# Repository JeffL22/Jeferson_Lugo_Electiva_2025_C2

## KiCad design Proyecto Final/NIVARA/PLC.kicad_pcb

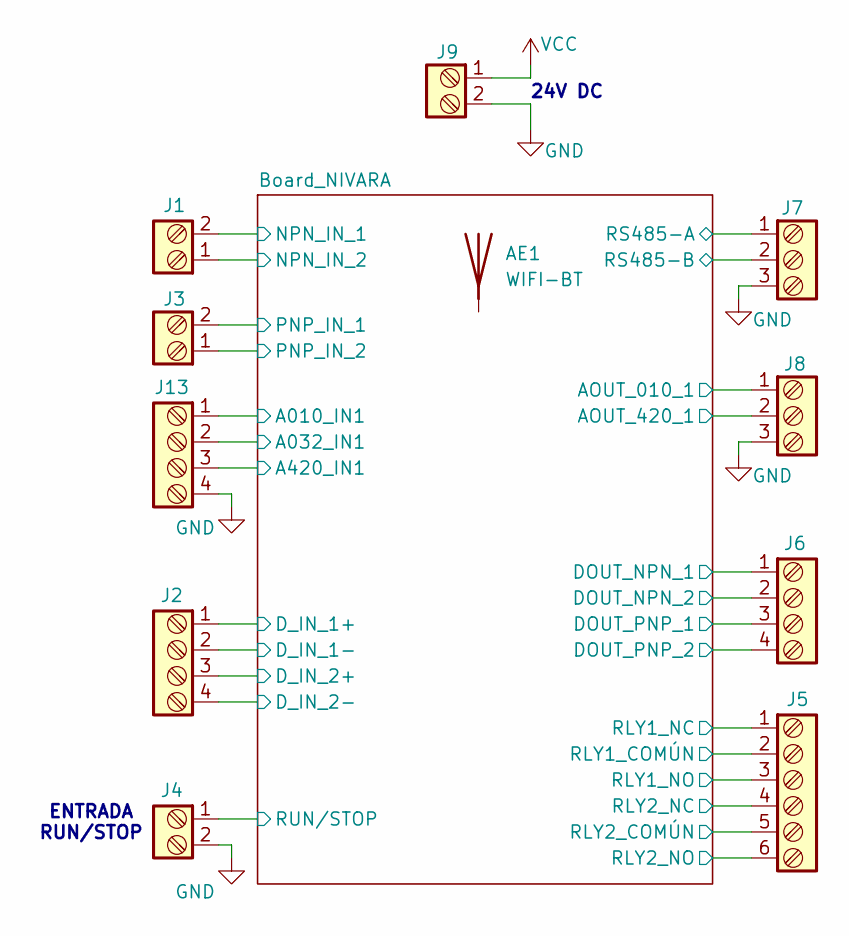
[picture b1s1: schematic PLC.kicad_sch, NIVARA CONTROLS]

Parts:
AE1: WIFI-BT
J1, J3, J4, J9: Screw_Terminal_2_P5.00mm; TerminalBlock_Phoenix_PT-1,5-2-5.0-H_1x02_P5.00mm_Horizontal
J2, J6, J13: Screw_Terminal_4_P5.00mm; TerminalBlock_Phoenix_PT-1,5-4-5.0-H_1x04_P5.00mm_Horizontal
J5: Screw_Terminal_6_P5.00mm; TerminalBlock_Phoenix_PT-1,5-6-5.0-H_1x06_P5.00mm_Horizontal
J7, J8: Screw_Terminal_3_P5.00mm; TerminalBlock_Phoenix_PT-1,5-3-5.0-H_1x03_P5.00mm_Horizontal

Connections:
/Board_NIVARA/A010_IN1: J13.1; also elsewhere on the board
/Board_NIVARA/A032_IN1: J13.2; also elsewhere on the board
/Board_NIVARA/A420_IN1: J13.3; also elsewhere on the board
/Board_NIVARA/AOUT_010_1: J8.1; also elsewhere on the board
/Board_NIVARA/AOUT_420_1: J8.2; also elsewhere on the board
/Board_NIVARA/DOUT_NPN_1: J6.1; also elsewhere on the board
/Board_NIVARA/DOUT_NPN_2: J6.2; also elsewhere on the board
/Board_NIVARA/DOUT_PNP_1: J6.3; also elsewhere on the board
/Board_NIVARA/DOUT_PNP_2: J6.4; also elsewhere on the board
/Board_NIVARA/D_IN_1+: J2.1; also elsewhere on the board
/Board_NIVARA/D_IN_2+: J2.3; also elsewhere on the board
/Board_NIVARA/NPN_IN_1: J1.2; also elsewhere on the board
/Board_NIVARA/NPN_IN_2: J1.1; also elsewhere on the board
/Board_NIVARA/PNP_IN_1: J3.2; also elsewhere on the board
/Board_NIVARA/PNP_IN_2: J3.1; also elsewhere on the board
/Board_NIVARA/RLY1_COMÚN: J5.2; also elsewhere on the board
/Board_NIVARA/RLY1_NC: J5.1; also elsewhere on the board
/Board_NIVARA/RLY1_NO: J5.3; also elsewhere on the board
/Board_NIVARA/RLY2_COMÚN: J5.5; also elsewhere on the board
/Board_NIVARA/RLY2_NC: J5.4; also elsewhere on the board
/Board_NIVARA/RLY2_NO: J5.6; also elsewhere on the board
/Board_NIVARA/RS485-A: J7.1; also elsewhere on the board
/Board_NIVARA/RS485-B: J7.2; also elsewhere on the board
/Board_NIVARA/RUN/STOP: J4.1
GND: J2.2, J2.4, J4.2, J7.3, J8.3, J9.2, J13.4; also elsewhere on the board
VCC: J9.1; also elsewhere on the board

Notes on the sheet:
24V DC
ENTRADA RUN/STOP

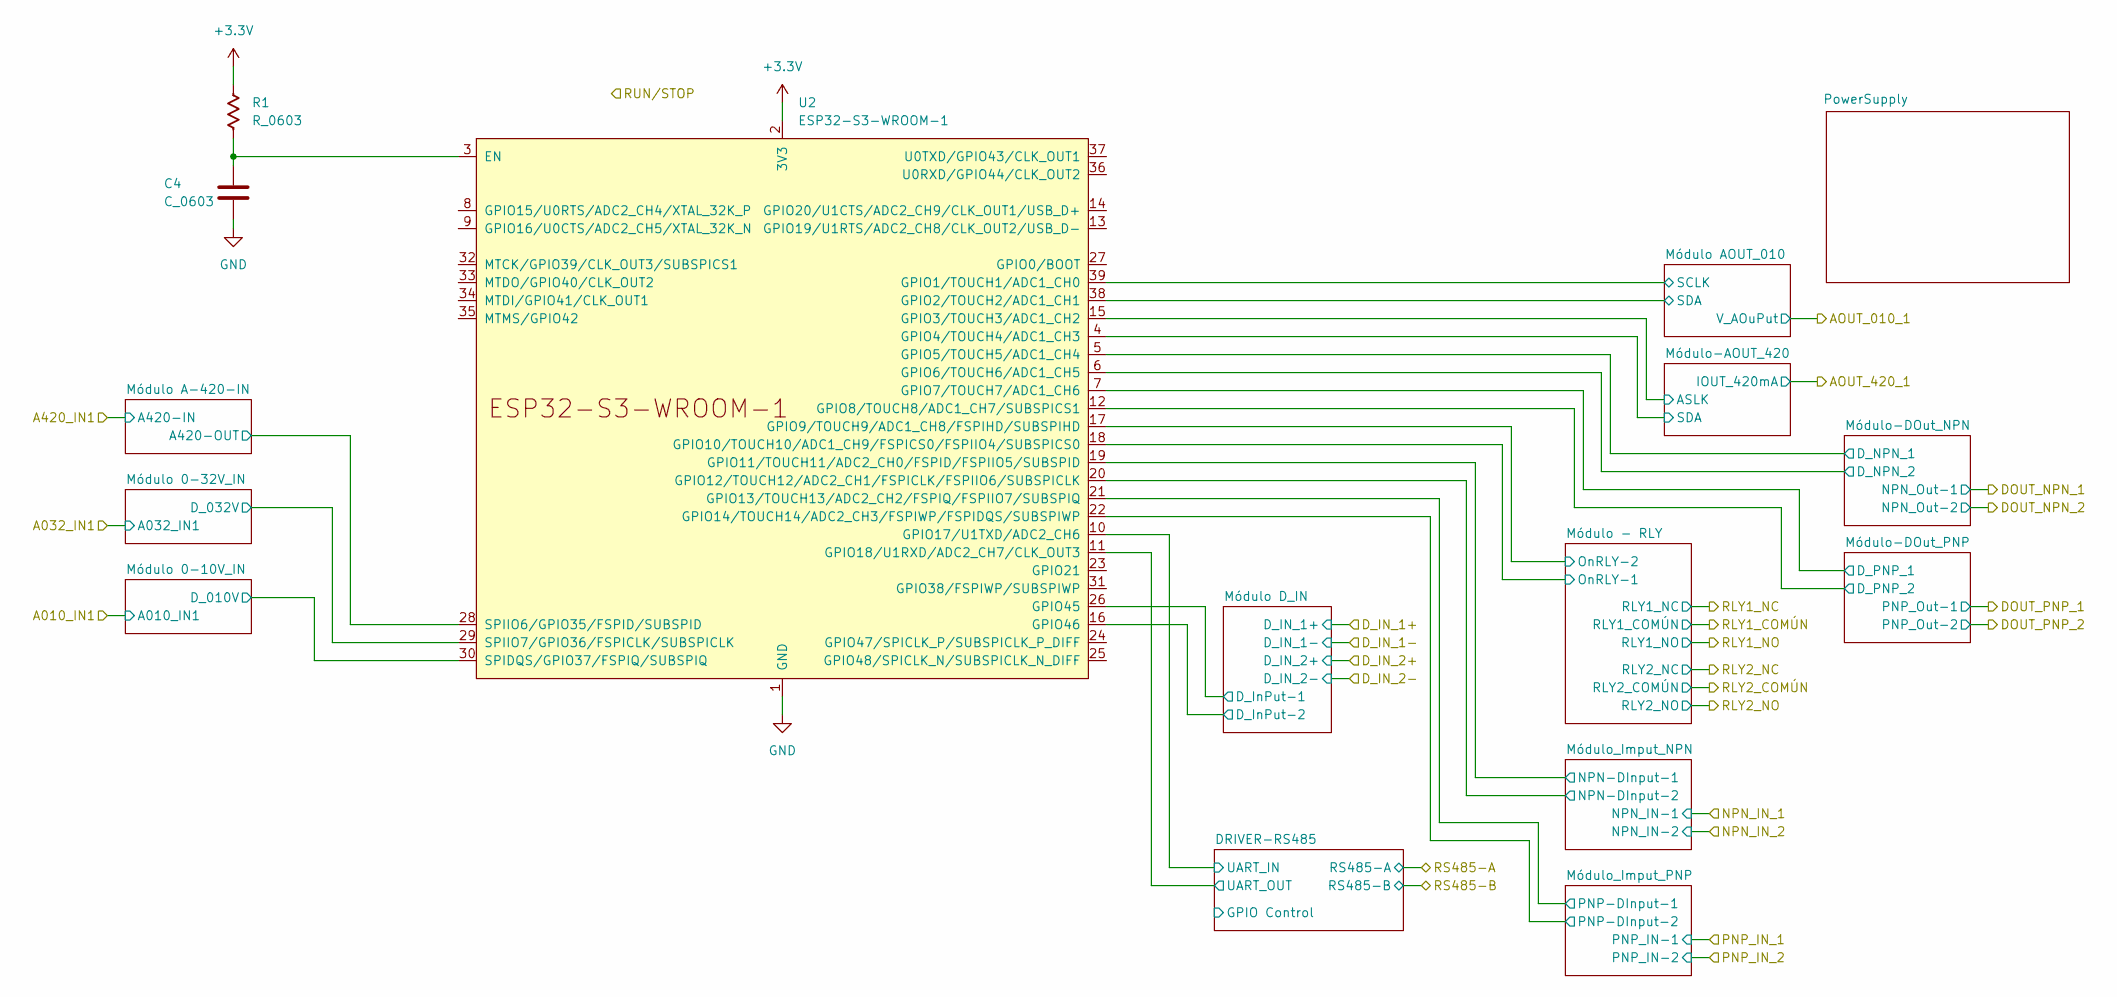
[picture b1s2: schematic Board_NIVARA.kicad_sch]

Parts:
C4: C_0603; C_0603_1608Metric
R1: R_0603; R_0603_1608Metric
U2: ESP32-S3-WROOM-1

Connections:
+3.3V: R1.1, U2.2 (3V3); also elsewhere on the board
/Board_NIVARA/A420_IN1: U2.28 (SPIIO6/GPIO35/FSPID/SUBSPID); also elsewhere on the board
/Board_NIVARA/DRIVER-RS485/UART_IN: U2.10 (GPIO17/U1TXD/ADC2_CH6); also elsewhere on the board
/Board_NIVARA/DRIVER-RS485/UART_OUT: U2.11 (GPIO18/U1RXD/ADC2_CH7/CLK_OUT3); also elsewhere on the board
/Board_NIVARA/Módulo 0-10V_IN/D_010V: U2.30 (SPIDQS/GPIO37/FSPIQ/SUBSPIQ); also elsewhere on the board
/Board_NIVARA/Módulo 0-32V_IN/D_032V: U2.29 (SPIIO7/GPIO36/FSPICLK/SUBSPICLK); also elsewhere on the board
/Board_NIVARA/Módulo - RLY/OnRLY-1: U2.18 (GPIO10/TOUCH10/ADC1_CH9/FSPICS0/FSPIIO4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); also elsewhere on the board
/Board_NIVARA/Módulo - RLY/OnRLY-2: U2.17 (GPIO9/TOUCH9/ADC1_CH8/FSPIHD/SUBSPIHD); also elsewhere on the board
/Board_NIVARA/Módulo AOUT_010/SCLK: U2.39 (GPIO1/TOUCH1/ADC1_CH0); also elsewhere on the board
/Board_NIVARA/Módulo AOUT_010/SDA: U2.38 (GPIO2/TOUCH2/ADC1_CH1); also elsewhere on the board
/Board_NIVARA/Módulo D_IN/D_InPut-1: U2.26 (GPIO45); also elsewhere on the board
/Board_NIVARA/Módulo D_IN/D_InPut-2: U2.16 (GPIO46); also elsewhere on the board
/Board_NIVARA/Módulo-AOUT_420/ASLK: U2.15 (GPIO3/TOUCH3/ADC1_CH2); also elsewhere on the board
/Board_NIVARA/Módulo-AOUT_420/SDA: U2.4 (GPIO4/TOUCH4/ADC1_CH3); also elsewhere on the board
/Board_NIVARA/Módulo-DOut_NPN/D_NPN_1: U2.5 (GPIO5/TOUCH5/ADC1_CH4); also elsewhere on the board
/Board_NIVARA/Módulo-DOut_NPN/D_NPN_2: U2.6 (GPIO6/TOUCH6/ADC1_CH5); also elsewhere on the board
/Board_NIVARA/Módulo-DOut_PNP/D_PNP_1: U2.7 (GPIO7/TOUCH7/ADC1_CH6); also elsewhere on the board
/Board_NIVARA/Módulo-DOut_PNP/D_PNP_2: U2.12 (GPIO8/TOUCH8/ADC1_CH7/SUBSPICS1); also elsewhere on the board
/Board_NIVARA/Módulo_Imput_NPN/NPN-DInput-1: U2.19 (GPIO11/TOUCH11/ADC2_CH0/FSPID/FSPIIO5/S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); also elsewhere on the board
/Board_NIVARA/Módulo_Imput_NPN/NPN-DInput-2: U2.20 (GPIO12/TOUCH12/ADC2_CH1/FSPICLK/FSPIIO6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); also elsewhere on the board
/Board_NIVARA/Módulo_Imput_PNP/PNP-DInput-1: U2.21 (GPIO13/TOUCH13/ADC2_CH2/FSPIQ/FSPIIO7/S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); also elsewhere on the board
/Board_NIVARA/Módulo_Imput_PNP/PNP-DInput-2: U2.22 (GPIO14/TOUCH14/ADC2_CH3/FSPIWP/FSPIDQS/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); also elsewhere on the board
GND: C4.2, U2.1 (GND), U2.40 (GND), U2.41 (GND); also elsewhere on the board
unnamed: C4.1, R1.2, U2.3 (EN)

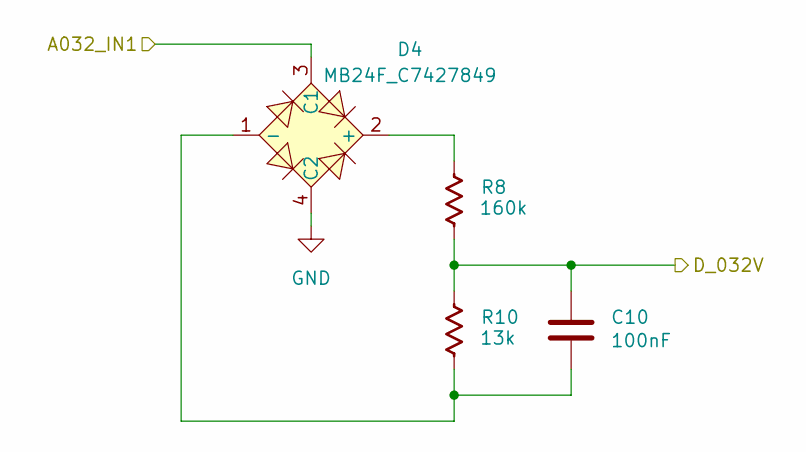
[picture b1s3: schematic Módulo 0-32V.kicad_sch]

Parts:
C10: C_0805; C_0805_2012Metric
D4: MB24F_C7427849; MB24F-SMD_L4.7-W3.8-P2.50-LS6.8-BL; LCSC Part C7427849
R8, R10: R_0603; R_0603_1608Metric

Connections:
/Board_NIVARA/A032_IN1: D4.3 (C1); also elsewhere on the board
/Board_NIVARA/Módulo 0-32V_IN/D_032V: C10.1, R8.2, R10.1; also elsewhere on the board
GND: D4.4 (C2); also elsewhere on the board
unnamed: D4.2 (+), R8.1
unnamed: C10.2, D4.1 (-), R10.2

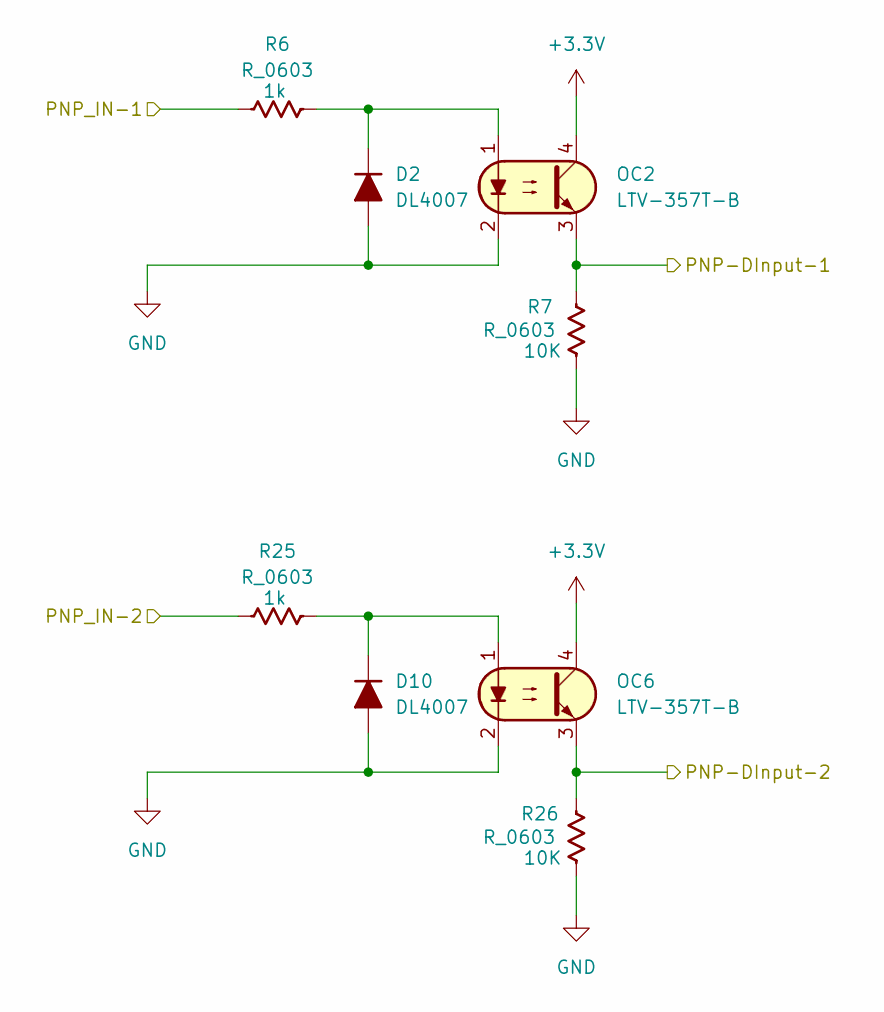
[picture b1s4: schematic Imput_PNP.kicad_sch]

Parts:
D2, D10: DL4007; D_0805_2012Metric_Pad1.15x1.40mm_HandSolder
OC2, OC6: LTV-357T-B; SO-4_4.4x3.9mm_P2.54mm
R6, R7, R25, R26: R_0603; R_0603_1608Metric

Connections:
+3.3V: OC2.4, OC6.4; also elsewhere on the board
/Board_NIVARA/Módulo_Imput_PNP/PNP-DInput-1: OC2.3, R7.2; also elsewhere on the board
/Board_NIVARA/Módulo_Imput_PNP/PNP-DInput-2: OC6.3, R26.2; also elsewhere on the board
/Board_NIVARA/PNP_IN_1: R6.1; also elsewhere on the board
/Board_NIVARA/PNP_IN_2: R25.1; also elsewhere on the board
GND: D2.2 (A), D10.2 (A), OC2.2, OC6.2, R7.1, R26.1; also elsewhere on the board
unnamed: D2.1 (K), OC2.1, R6.2
unnamed: D10.1 (K), OC6.1, R25.2

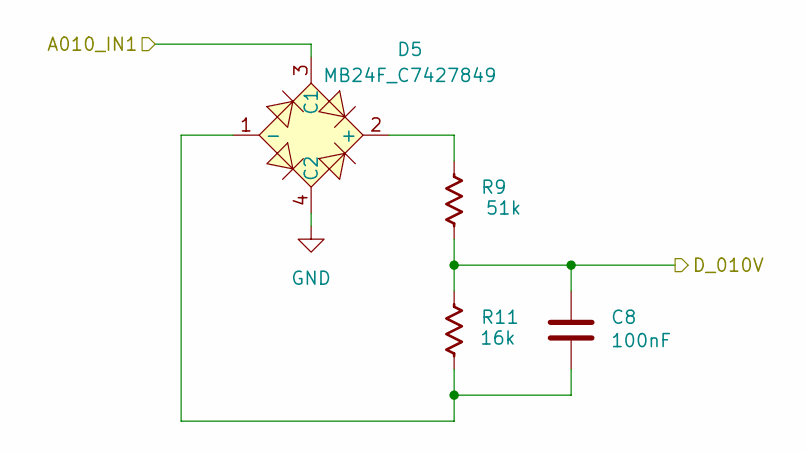
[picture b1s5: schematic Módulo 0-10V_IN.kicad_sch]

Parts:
C8: C_0805; C_0805_2012Metric
D5: MB24F_C7427849; MB24F-SMD_L4.7-W3.8-P2.50-LS6.8-BL; LCSC Part C7427849
R9, R11: R_0603; R_0603_1608Metric

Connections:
/Board_NIVARA/A010_IN1: D5.3 (C1); also elsewhere on the board
/Board_NIVARA/Módulo 0-10V_IN/D_010V: C8.1, R9.2, R11.1; also elsewhere on the board
GND: D5.4 (C2); also elsewhere on the board
unnamed: D5.2 (+), R9.1
unnamed: C8.2, D5.1 (-), R11.2

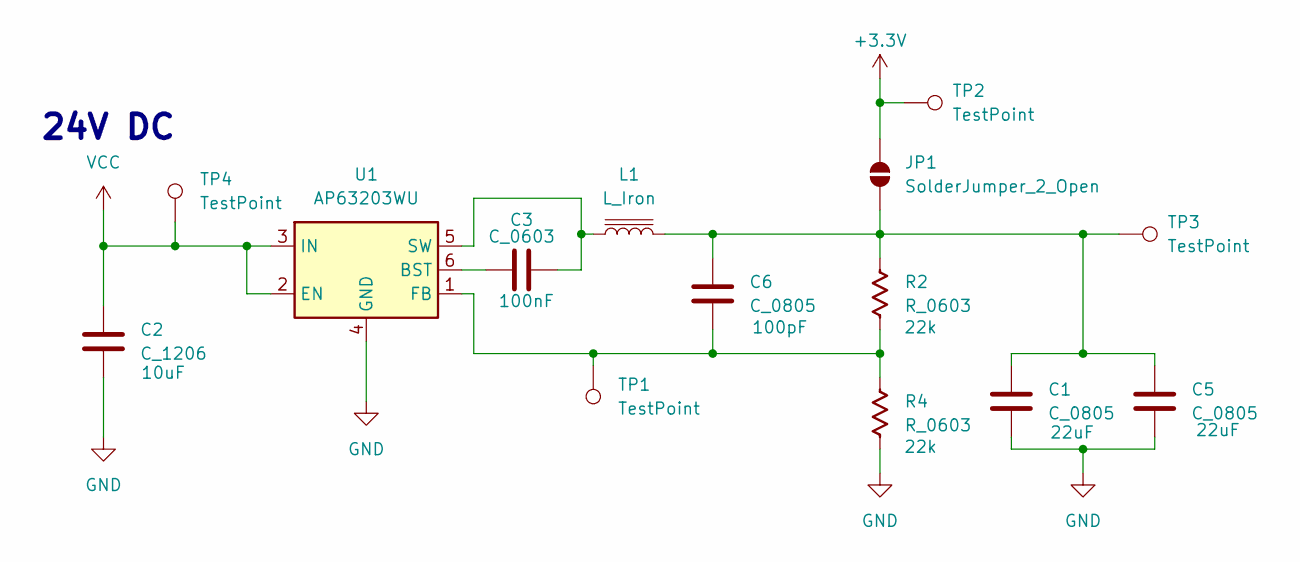
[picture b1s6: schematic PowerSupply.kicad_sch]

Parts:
C1, C5, C6: C_0805; C_0805_2012Metric
C2: C_1206; C_1206_3216Metric
C3: C_0603; C_0603_1608Metric
JP1: SolderJumper_2_Open; SolderJumper-2_P1.3mm_Open_RoundedPad1.0x1.5mm
L1: L_Iron; L_Bourns-SRN6028
R2, R4: R_0603; R_0603_1608Metric
TP1, TP2, TP3, TP4: TestPoint; TestPoint_Keystone_5015_Micro_Mini
U1: AP63203WU; TSOT-23-6

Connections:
+3.3V: JP1.2 (B), TP2.1; also elsewhere on the board
GND: C1.2, C2.2, C5.2, R4.2, U1.4 (GND); also elsewhere on the board
unnamed: C1.1, C5.1, C6.1, JP1.1 (A), L1.2, R2.1, TP3.1
unnamed: C3.1, U1.6 (BST)
unnamed: C6.2, R2.2, R4.1, TP1.1, U1.1 (FB)
unnamed: C3.2, L1.1, U1.5 (SW)
VCC: C2.1, TP4.1, U1.2 (EN), U1.3 (IN); also elsewhere on the board

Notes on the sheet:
24V DC

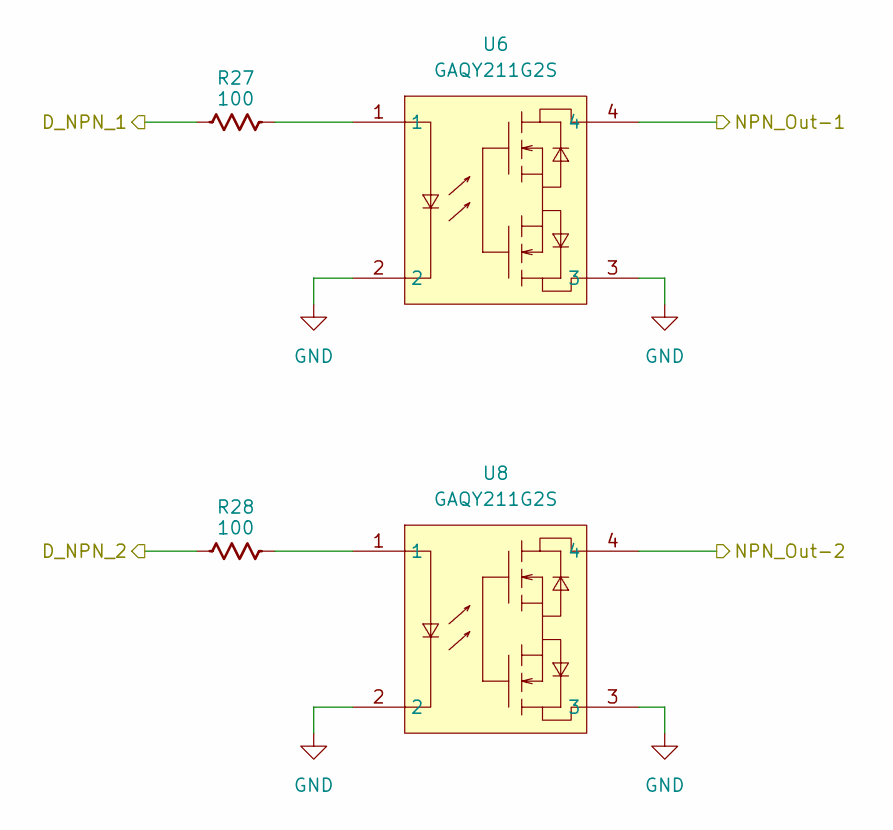
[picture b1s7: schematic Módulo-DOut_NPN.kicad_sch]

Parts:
R27, R28: R_0603; R_0603_1608Metric
U6, U8: GAQY211G2S; SOP-4_L4.4-W4.3-P2.54-LS6.8-BL; LCSC Part C7435104

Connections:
/Board_NIVARA/DOUT_NPN_1: U6.4; also elsewhere on the board
/Board_NIVARA/DOUT_NPN_2: U8.4; also elsewhere on the board
/Board_NIVARA/Módulo-DOut_NPN/D_NPN_1: R27.1; also elsewhere on the board
/Board_NIVARA/Módulo-DOut_NPN/D_NPN_2: R28.1; also elsewhere on the board
GND: U6.2, U6.3, U8.2, U8.3; also elsewhere on the board
unnamed: R27.2, U6.1
unnamed: R28.2, U8.1

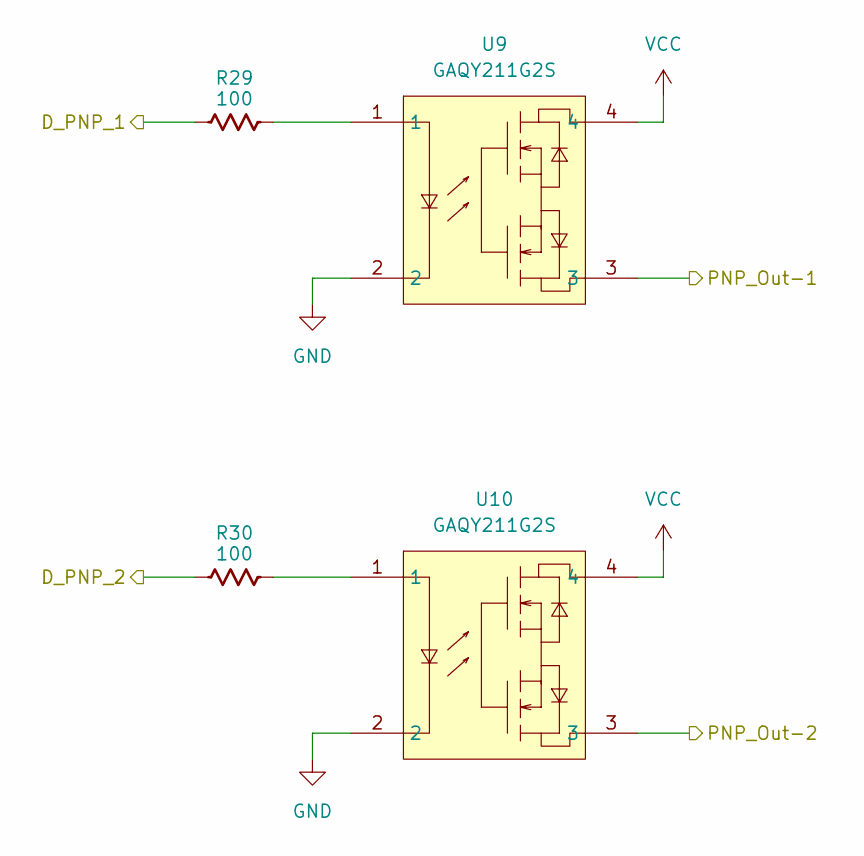
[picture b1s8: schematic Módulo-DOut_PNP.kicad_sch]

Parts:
R29, R30: R_0603; R_0603_1608Metric
U9, U10: GAQY211G2S; SOP-4_L4.4-W4.3-P2.54-LS6.8-BL; LCSC Part C7435104

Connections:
/Board_NIVARA/DOUT_PNP_1: U9.3; also elsewhere on the board
/Board_NIVARA/DOUT_PNP_2: U10.3; also elsewhere on the board
/Board_NIVARA/Módulo-DOut_PNP/D_PNP_1: R29.1; also elsewhere on the board
/Board_NIVARA/Módulo-DOut_PNP/D_PNP_2: R30.1; also elsewhere on the board
GND: U9.2, U10.2; also elsewhere on the board
unnamed: R29.2, U9.1
unnamed: R30.2, U10.1
VCC: U9.4, U10.4; also elsewhere on the board

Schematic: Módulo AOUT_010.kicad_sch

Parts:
C11, C12: C_0603; C_0603_1608Metric
D8: SMF24A; D_SOD-123F
R17, R23, R24: R_0603; R_0603_1608Metric
U7: GP8201S-TC50-EW; GP8201S; LCSC Part C5240058

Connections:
+3.3V: R23.1, R24.1; also elsewhere on the board
/Board_NIVARA/AOUT_010_1: C12.2, D8.1 (K), U7.6 (VOUT); also elsewhere on the board
/Board_NIVARA/Módulo AOUT_010/SCLK: R23.2, U7.1 (SCLK); also elsewhere on the board
/Board_NIVARA/Módulo AOUT_010/SDA: R24.2, U7.2 (SDA); also elsewhere on the board
GND: C11.1, C12.1, D8.2 (A), U7.5 (GND); also elsewhere on the board
unnamed: R17.2, U7.7 (SEL)
unnamed: C11.2, R17.1, U7.8 (V5V)
VCC: U7.4 (VCC); also elsewhere on the board

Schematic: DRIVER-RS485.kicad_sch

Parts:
C7: C_1206; C_1206_3216Metric
D1: SM712; SOT-23
U4: C2992406

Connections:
+3.3V: C7.1, D1.2 (A2), U4.1 (VCC); also elsewhere on the board
/Board_NIVARA/DRIVER-RS485/GPIO Control: U4.5 (CON)
/Board_NIVARA/DRIVER-RS485/UART_IN: U4.3 (TXD); also elsewhere on the board
/Board_NIVARA/DRIVER-RS485/UART_OUT: U4.4 (RXD); also elsewhere on the board
/Board_NIVARA/RS485-A: U4.9 (A); also elsewhere on the board
/Board_NIVARA/RS485-B: U4.8 (B); also elsewhere on the board
GND: C7.2, D1.1 (A1), D1.3 (Com), U4.2 (GND); also elsewhere on the board

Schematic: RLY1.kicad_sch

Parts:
K1, K3: SRA-24VDC-CL; RELAY-TH_SRA-X-CX; LCSC Part C127865
U3: LK1802; LCSC Part C2984831

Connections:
/Board_NIVARA/Módulo - RLY/OnRLY-1: U3.3 (1B); also elsewhere on the board
/Board_NIVARA/Módulo - RLY/OnRLY-2: U3.4 (2B); also elsewhere on the board
/Board_NIVARA/RLY1_COMÚN: K3.5; also elsewhere on the board
/Board_NIVARA/RLY1_NC: K3.2; also elsewhere on the board
/Board_NIVARA/RLY1_NO: K3.1; also elsewhere on the board
/Board_NIVARA/RLY2_COMÚN: K1.5; also elsewhere on the board
/Board_NIVARA/RLY2_NC: K1.2; also elsewhere on the board
/Board_NIVARA/RLY2_NO: K1.1; also elsewhere on the board
GND: U3.2 (E); also elsewhere on the board
unnamed: K3.4, U3.1 (1C)
unnamed: K1.4, U3.6 (2C)
VCC: K1.3, K3.3, U3.5 (COM); also elsewhere on the board

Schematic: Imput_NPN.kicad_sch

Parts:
D3, D9: DL4007; D_0805_2012Metric_Pad1.15x1.40mm_HandSolder
OC1, OC5: LTV-357T-B; SO-4_4.4x3.9mm_P2.54mm
R3, R5, R18, R19: R_0603; R_0603_1608Metric

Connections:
+3.3V: R5.2, R19.2; also elsewhere on the board
/Board_NIVARA/Módulo_Imput_NPN/NPN-DInput-1: OC1.4, R5.1; also elsewhere on the board
/Board_NIVARA/Módulo_Imput_NPN/NPN-DInput-2: OC5.4, R19.1; also elsewhere on the board
/Board_NIVARA/NPN_IN_1: R3.1; also elsewhere on the board
/Board_NIVARA/NPN_IN_2: R18.1; also elsewhere on the board
GND: D3.2 (A), D9.2 (A), OC1.2, OC1.3, OC5.2, OC5.3; also elsewhere on the board
unnamed: D3.1 (K), OC1.1, R3.2
unnamed: D9.1 (K), OC5.1, R18.2

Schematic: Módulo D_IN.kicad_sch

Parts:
D6, D7: DL4007; D_0805_2012Metric_Pad1.15x1.40mm_HandSolder
OC3, OC4: LTV-357T-B; SO-4_4.4x3.9mm_P2.54mm
R13, R14, R15, R16: R_0603; R_0603_1608Metric

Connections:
+3.3V: R14.1, R16.1; also elsewhere on the board
/Board_NIVARA/D_IN_1+: R13.1; also elsewhere on the board
/Board_NIVARA/D_IN_2+: R15.1; also elsewhere on the board
/Board_NIVARA/Módulo D_IN/D_InPut-1: OC3.4, R14.2; also elsewhere on the board
/Board_NIVARA/Módulo D_IN/D_InPut-2: OC4.4, R16.2; also elsewhere on the board
GND: D6.2 (A), D7.2 (A), OC3.2, OC3.3, OC4.2, OC4.3; also elsewhere on the board
unnamed: D6.1 (K), OC3.1, R13.2
unnamed: D7.1 (K), OC4.1, R15.2

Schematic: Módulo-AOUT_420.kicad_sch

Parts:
C13, C14: C_0603; C_0603_1608Metric
R20, R21, R22: R_0603; R_0603_1608Metric
U5: GP8303-TC50-EW; ESOP-10_L4.9-W3.9-P1.00-LS6.1-BL-EP; LCSC Part C3445809

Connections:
+3.3V: R20.1, R21.1; also elsewhere on the board
/Board_NIVARA/AOUT_420_1: U5.8 (IOUT); also elsewhere on the board
/Board_NIVARA/Módulo-AOUT_420/ASLK: R20.2, U5.1 (SLCK); also elsewhere on the board
/Board_NIVARA/Módulo-AOUT_420/SDA: R21.2, U5.2 (SDA); also elsewhere on the board
GND: C13.2, C14.1, R22.2, U5.3 (A0), U5.4 (A1), U5.6 (GND), U5.9 (A2); also elsewhere on the board
unnamed: C13.1, R22.1, U5.7 (SET)
unnamed: C14.2, U5.10 (V5V)
VCC: U5.5 (VCC); also elsewhere on the board

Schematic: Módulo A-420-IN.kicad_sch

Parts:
C9: C_0603; C_0603_1608Metric
R12: R_0603; R_0603_1608Metric

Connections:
/Board_NIVARA/A420_IN1: C9.1, R12.1; also elsewhere on the board
GND: C9.2, R12.2; also elsewhere on the board

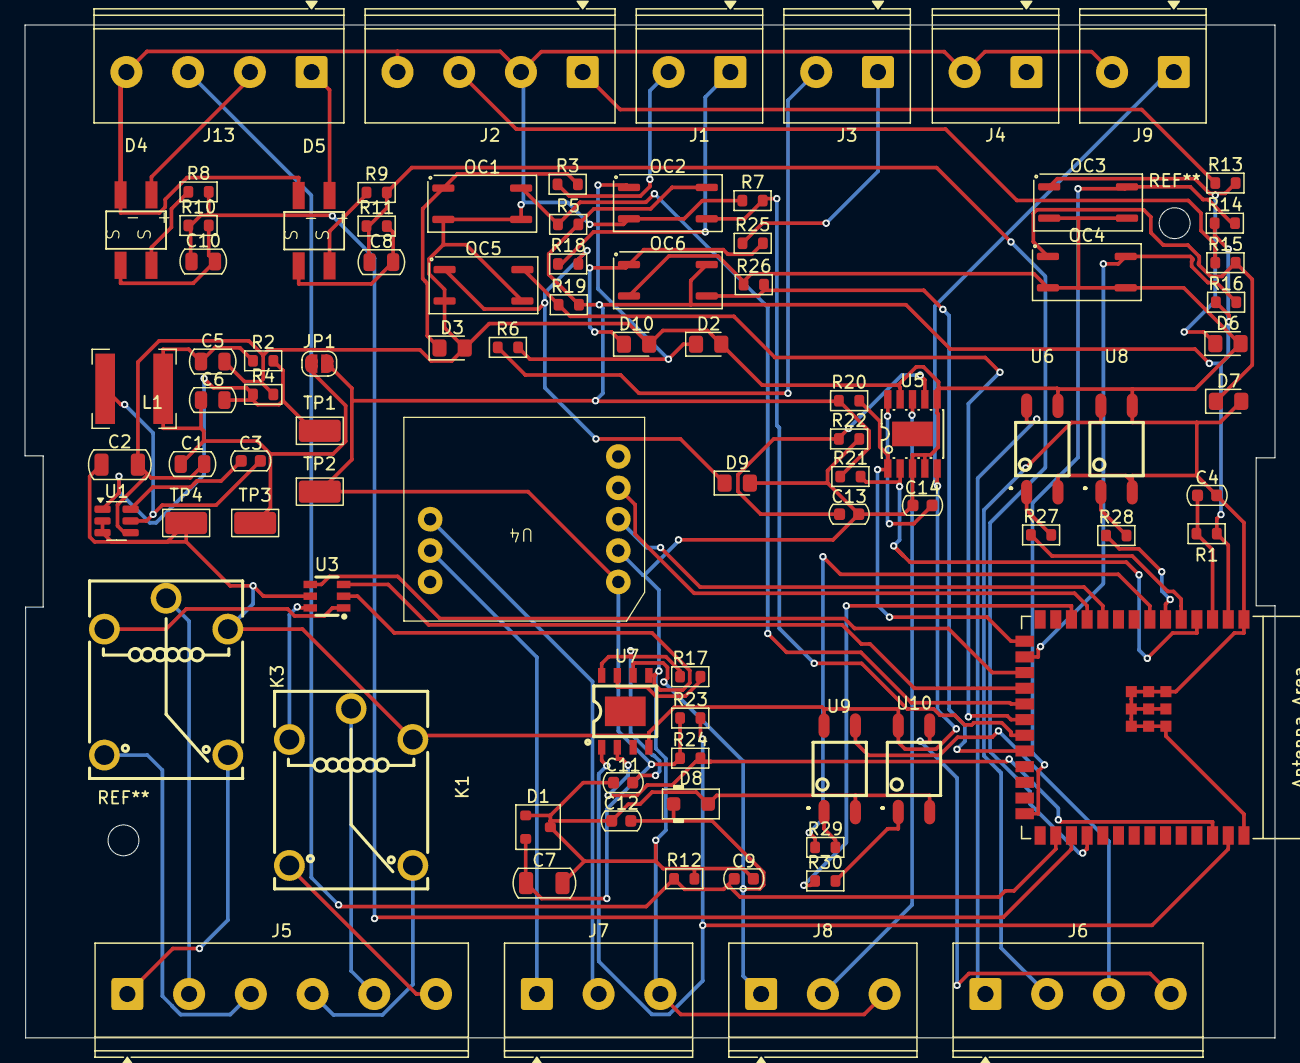
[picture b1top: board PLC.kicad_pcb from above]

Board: 2 copper layers, 101.2 x 82.0 mm, 88 parts (0 on the bottom side), 71 nets.

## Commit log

2025-05-16 Prueba
    Esta es una prueba del repositorio.
2025-05-17 Probando el repositorio de forma remota.
2025-05-17 Prueba 2
2025-05-17 Probando
2025-05-17 siygig
2025-05-17 Borrando Pruebas
2025-05-23 Tarea #1 (Los Requerimientos)
2025-05-29 Diseños 3D (Carcasa de PLC)
2025-05-29 Actualización
2025-06-06 Actualización: Etiqueta de producto. Garabato. Investigación. Inicio de Doc.
2025-06-13 Avances de NIRVANA/SORIONX
2025-06-13 Actualización de Nombre.
2025-06-20 Tarea #4
2025-07-03 Actualización.
2025-07-04 Investigación de tarea 5
2025-07-30 Avances en PCB
2025-08-22 Actualización de Diseño 3D e Inicio de enrutado.
